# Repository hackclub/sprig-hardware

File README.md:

# This repository has been deprecated. This project is now maintained at https://github.com/hackclub/sprig/tree/main/hardware
## If you're looking for instructions on assembling your sprig, check out our [assembly guide!](https://github.com/hackclub/sprig/blob/main/docs/ASSEMBLY.md)

---

## The Sprig Console

You can find KiCAD 6 files for the PCB of Sprig, a BOM, and CAD models for the acrylic back covers here.

- `hardware/` contains the KiCAD files and Bill of Materials for the PCB
- `back_covers/` contains the CAD models for the acrylic back covers

The main [Sprig Repo is available here](https://www.github.com/hackclub/sprig).

# Description

The Sprig console is a custom-designed, limited edition game console powered by the Raspberry Pi Pico. It has a 1.8" 160x128 LCD display, as well as eight tactile buttons for input. It uses two AAA batteries for power, and has a MAX98357A audio amplifier with an 8 ohm, 300mW Speaker.

The Sprig console is a custom-designed, limited edition game console built to run games written with the Sprig game editor.

It's powered by a Raspberry Pi RP2040, which is clocked at 125MHz, with 264kB SRAM and 2MB external QSPI flash. Four unused GPIO pins are exposed to the rear of the console.

The Sprig is powered by two AAA batteries. There is also a high efficiency schottky diode to prevent power flow to the batteries when connected to USB power.

In addition, there is a MAX98357A class D audio amplifier from Maxim Integrated, connected to a CUI Devices CVS-1508 8 ohm, 300mW speaker.

There are two LEDs for status, a power switch for batteries, as well as eight tactile buttons to control input.

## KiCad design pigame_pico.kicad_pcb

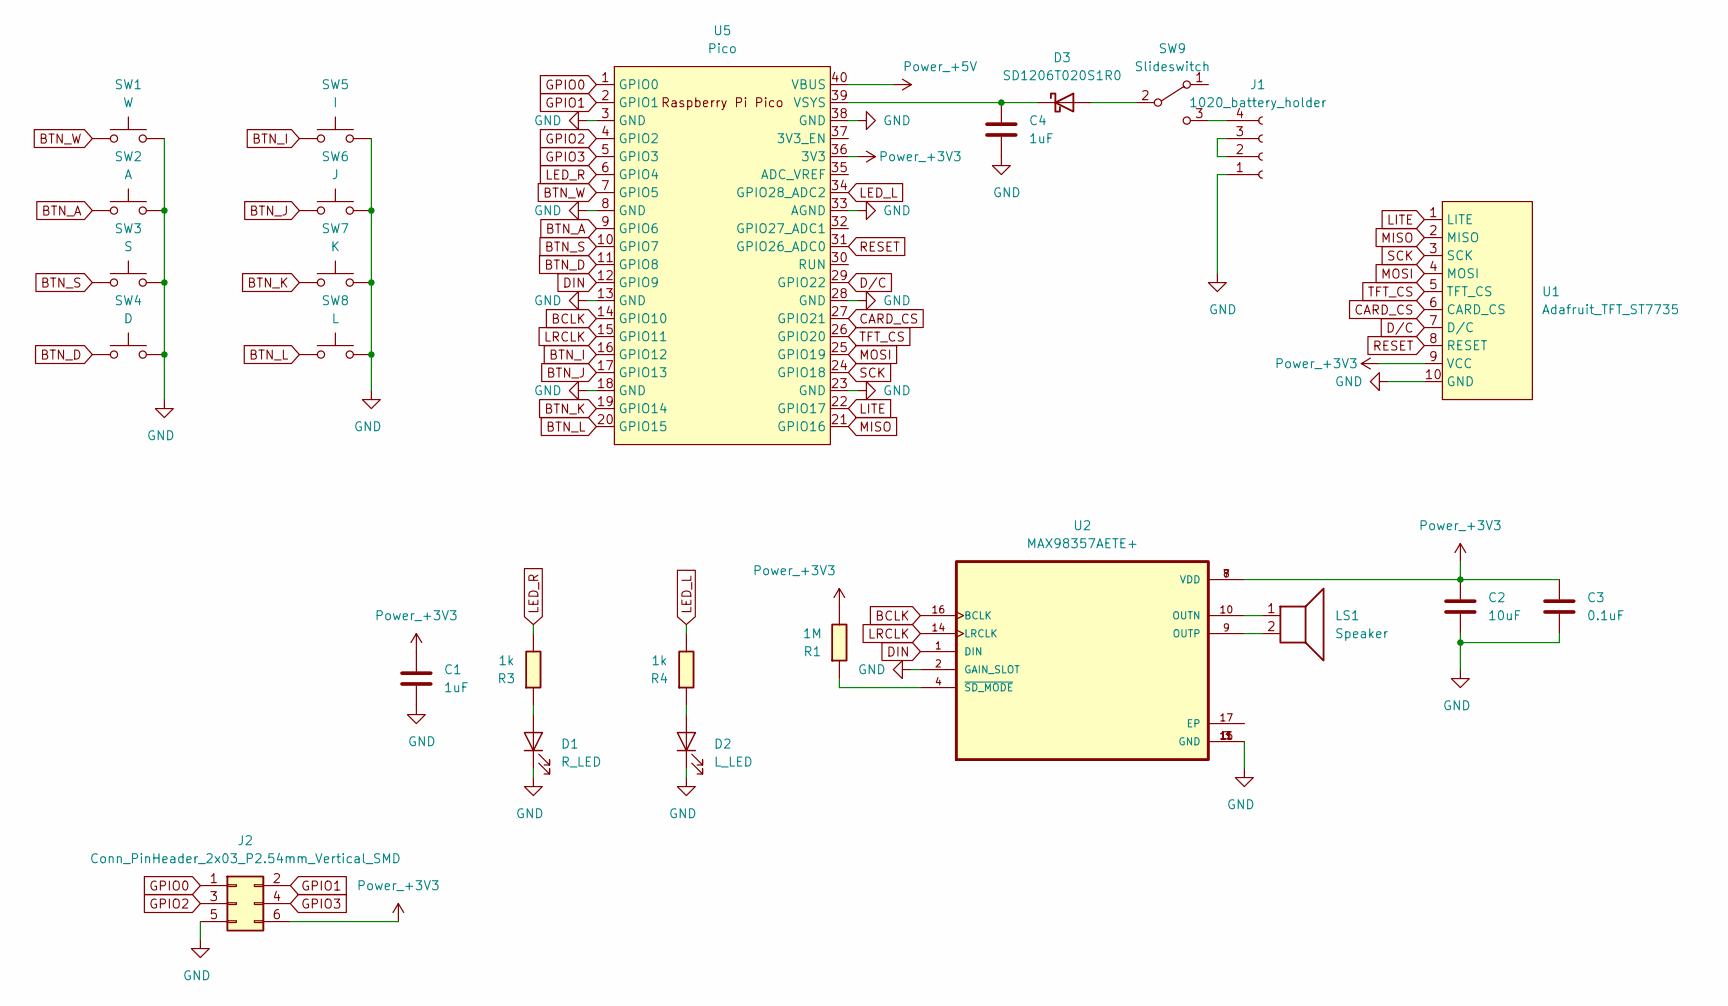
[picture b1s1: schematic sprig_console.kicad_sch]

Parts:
C1, C4: 1uF; C_1206
C2: 10uF; C_1206
C3: 0.1uF; C_1206
D1: R_LED; LED_1206
D2: L_LED; LED_1206
D3: SD1206T020S1R0; Diode_Schotky_100V_1A_Mini_SMA
J1: 1020_battery_holder; 1022
J2: Conn_PinHeader_2x03_P2.54mm_Vertical_SMD; PinHeader_2x03_P2.54mm_Vertical_SMD
LS1: Speaker; CVS-1508
R1: 1M; R_1206
R3, R4: 1k; R_1206
SW1: W; SW_PUSH-12mm_Wuerth-430476085716
SW2: A; SW_PUSH-12mm_Wuerth-430476085716
SW3: S; SW_PUSH-12mm_Wuerth-430476085716
SW4: D; SW_PUSH-12mm_Wuerth-430476085716
SW5: I; SW_PUSH-12mm_Wuerth-430476085716
SW6: J; SW_PUSH-12mm_Wuerth-430476085716
SW7: K; SW_PUSH-12mm_Wuerth-430476085716
SW8: L; SW_PUSH-12mm_Wuerth-430476085716
SW9: Slideswitch; slideswitchCK
U1: Adafruit_TFT_ST7735; TFT_ST7735
U2: MAX98357AETE+; QFN50P300X300X80-17N
U5: Pico; RPi_Pico_SMD_TH_mod

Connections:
+3V3: C1.1, C2.1, C3.1, J2.6, R1.1, U1.9 (VCC), U2.7 (VDD), U2.8 (VDD), U5.36 (3V3)
+5V: U5.40 (VBUS)
BCLK: U2.16 (BCLK), U5.14 (GPIO10)
BTN_A: SW2.1, U5.9 (GPIO6)
BTN_D: SW4.1, U5.11 (GPIO8)
BTN_I: SW5.1, U5.16 (GPIO12)
BTN_J: SW6.1, U5.17 (GPIO13)
BTN_K: SW7.1, U5.19 (GPIO14)
BTN_L: SW8.1, U5.20 (GPIO15)
BTN_S: SW3.1, U5.10 (GPIO7)
BTN_W: SW1.1, U5.7 (GPIO5)
CARD_CS: U1.6 (CARD_CS), U5.27 (GPIO21)
DIN: U2.1 (DIN), U5.12 (GPIO9)
D/C: U1.7 (D/C), U5.29 (GPIO22)
GND: C1.2, C2.2, C3.2, C4.2, D1.1 (K), D2.1 (K), J1.1, J2.5, SW1.2, SW2.2, SW3.2, SW4.2, SW5.2, SW6.2, SW7.2, SW8.2, U1.10 (GND), U2.2 (GAIN_SLOT), U2.3 (GND), U2.11 (GND), U2.15 (GND), U5.3 (GND), U5.8 (GND), U5.13 (GND), U5.18 (GND), U5.23 (GND), U5.28 (GND), U5.33 (AGND), U5.38 (GND)
GPIO0: J2.1, U5.1 (GPIO0)
GPIO1: J2.2, U5.2 (GPIO1)
GPIO2: J2.3, U5.4 (GPIO2)
GPIO3: J2.4, U5.5 (GPIO3)
LED_L: R4.1, U5.34 (GPIO28_ADC2)
LED_R: R3.1, U5.6 (GPIO4)
LITE: U1.1 (LITE), U5.22 (GPIO17)
LRCLK: U2.14 (LRCLK), U5.15 (GPIO11)
MISO: U1.2 (MISO), U5.21 (GPIO16)
MOSI: U1.4 (MOSI), U5.25 (GPIO19)
unnamed: C4.1, D3.1 (K), U5.39 (VSYS)
unnamed: D1.2 (A), R3.2
unnamed: D2.2 (A), R4.2
unnamed: D3.2 (A), SW9.2 (B)
unnamed: J1.2, J1.3
unnamed: J1.4, SW9.3 (C)
unnamed: LS1.1, U2.10 (OUTN)
unnamed: LS1.2, U2.9 (OUTP)
unnamed: R1.2, U2.4 (~SD_MODE)
RESET: U1.8 (RESET), U5.31 (GPIO26_ADC0)
SCK: U1.3 (SCK), U5.24 (GPIO18)
TFT_CS: U1.5 (TFT_CS), U5.26 (GPIO20)

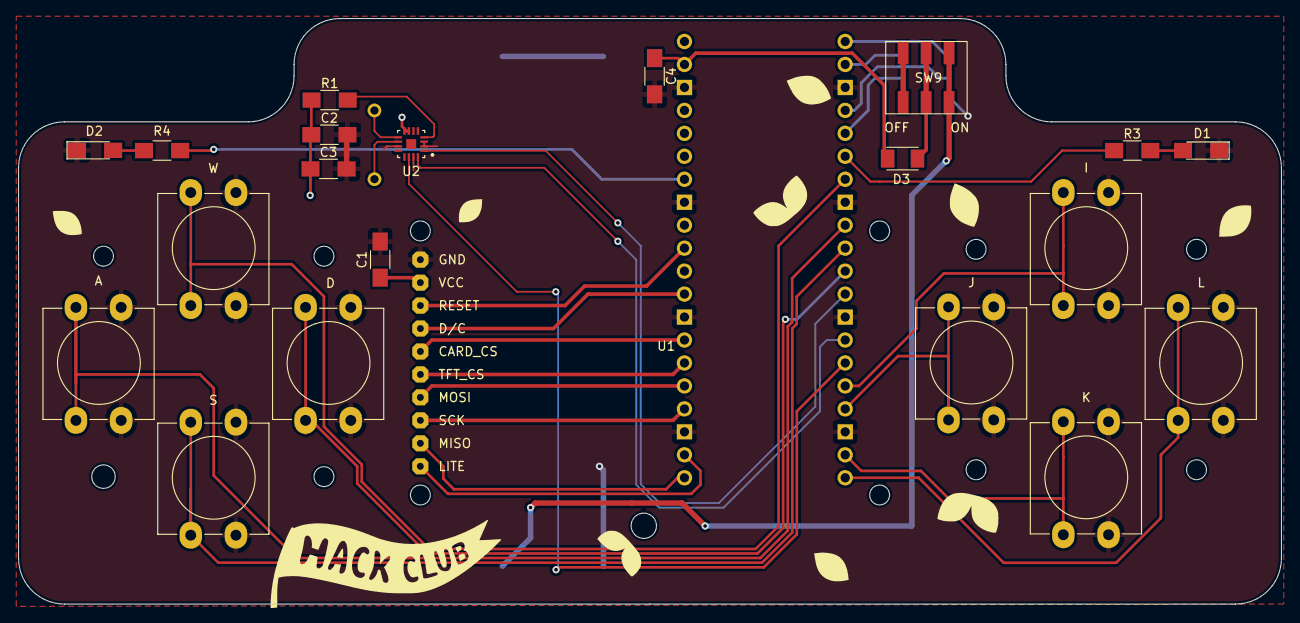
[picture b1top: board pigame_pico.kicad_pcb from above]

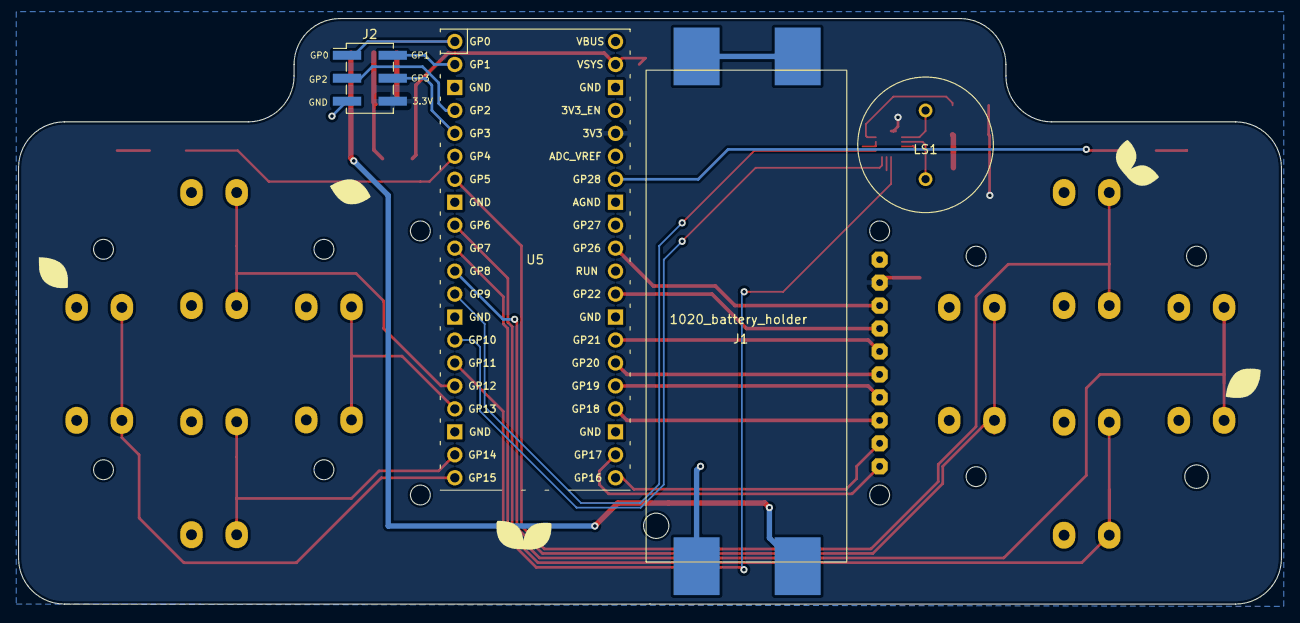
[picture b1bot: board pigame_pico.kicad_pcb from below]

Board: 2 copper layers, 139.7 x 64.8 mm, 25 parts (4 on the bottom side), 36 nets.

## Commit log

2022-08-25 init
2022-09-29 update copper text
2022-10-04 update hardware
2022-11-22 Update README.md
    add some information about sprig's hardware
2023-01-26 Update README.md
    update with more info
2023-01-26 Update README.md
    update links for images
2023-01-26 Add files for back covers
2023-03-19 Upload STLs separately
2023-03-19 Fix file name
2023-04-17 Format BoM list
2024-02-28 deprecate this repository
